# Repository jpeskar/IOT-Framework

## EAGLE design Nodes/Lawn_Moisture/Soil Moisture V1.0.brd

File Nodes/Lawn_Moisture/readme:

Lawn Moisture Sensor

Consists of a Vegetronix VH400 and two (2) Dallas DS18S20 one wire thermometers. The internal thermometer is used for tuning the radio and the external is for maping ground 
temperature.

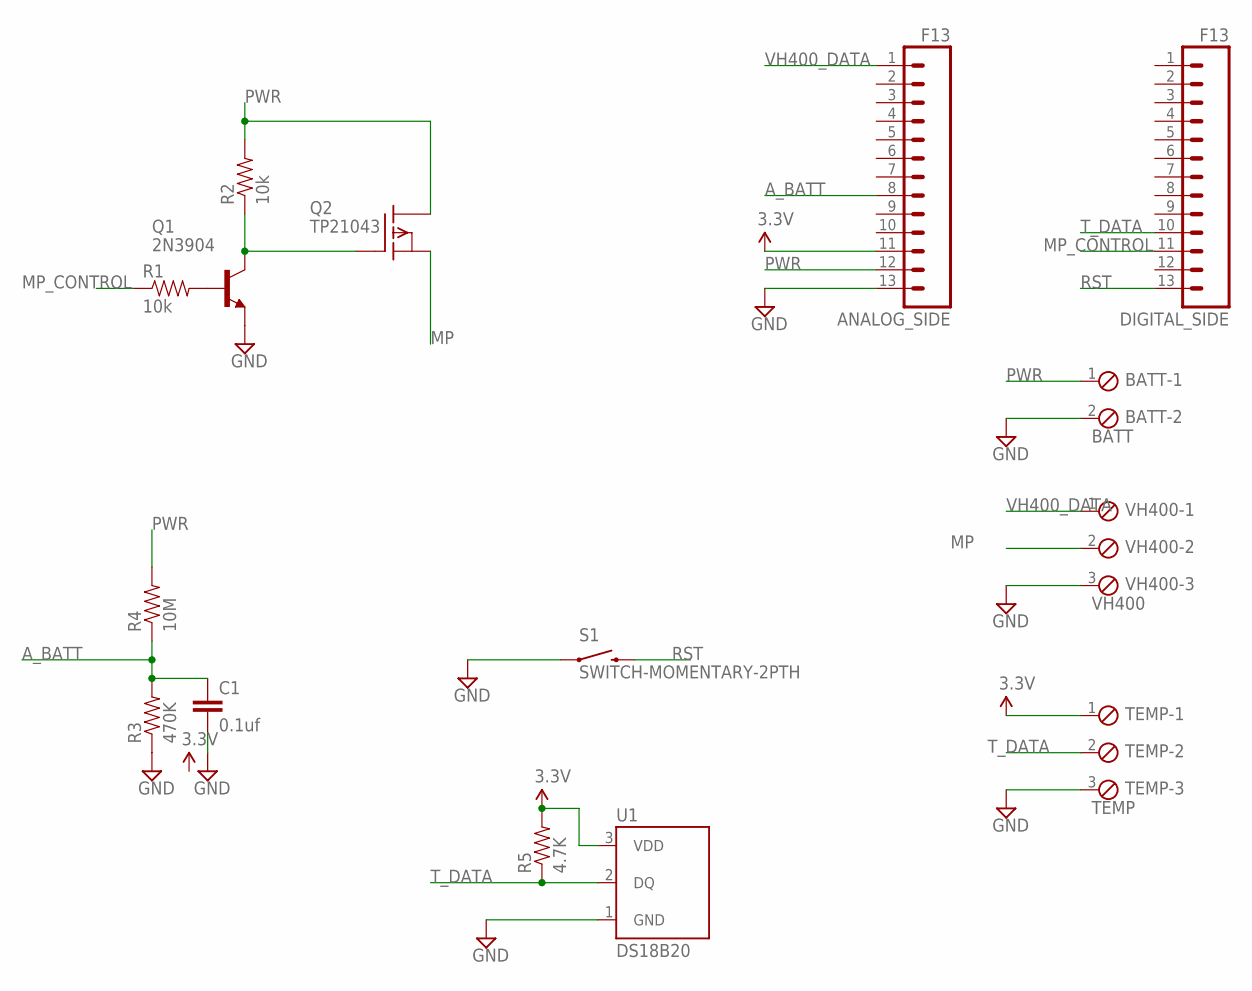
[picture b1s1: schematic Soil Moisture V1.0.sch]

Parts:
ANALOG_SIDE: F13; 1X13
BATT: BATT; 2POL254
C1: 0.1uf; CAP-PTH-SMALL-KIT
DIGITAL_SIDE: F13; 1X13
Q1: 2N3904; TO92
Q2: TP21043; TO92
R1, R2: 10k; AXIAL-0.3EZ
R3: 470K; AXIAL-0.3
R4: 10M; AXIAL-0.3
R5: 4.7K; AXIAL-0.3
S1: SWITCH-MOMENTARY-2PTH; TACTILE-PTH
TEMP: TEMP; 3POL254
U1: DS18B20; TO-92-AMMO
VH400: VH400; 3POL254

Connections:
3.3V: ANALOG_SIDE.11, R5.P$2 (2), TEMP.1, U1.3 (VDD)
A_BATT: ANALOG_SIDE.8, C1.1, R3.P$2 (2), R4.P$1 (1)
GND: ANALOG_SIDE.13, BATT.2, C1.2, Q1.3 (E), R3.P$1 (1), S1.1, TEMP.3, U1.1 (GND), VH400.3
MP: Q2.1 (S), VH400.2
MP_CONTROL: DIGITAL_SIDE.11, R1.P$1 (1)
unnamed: Q1.2 (B), R1.P$2 (2)
unnamed: Q1.1 (C), Q2.2 (G), R2.P$1 (1)
PWR: ANALOG_SIDE.12, BATT.1, Q2.3 (D), R2.P$2 (2), R4.P$2 (2)
RST: DIGITAL_SIDE.13, S1.3 (2)
T_DATA: DIGITAL_SIDE.10, R5.P$1 (1), TEMP.2, U1.2 (DQ)
VH400_DATA: ANALOG_SIDE.1, VH400.1

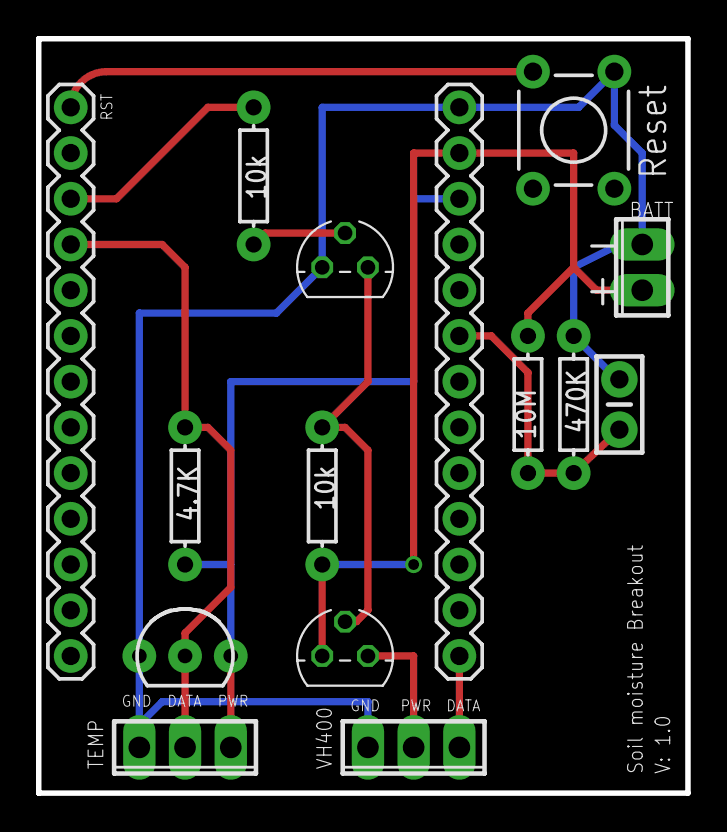
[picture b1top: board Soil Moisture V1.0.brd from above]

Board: 2 copper layers, 36.1 x 41.9 mm, 15 parts (0 on the bottom side), 11 nets.

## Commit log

2015-12-27 Create Lawn_Moisture
2015-12-27 Create Node_Libraries
2015-12-27 first commit of lawn moisture node
2015-12-27 code re-factoring
2015-12-28 re-factor new node functions
    Re-factored the capture of a new nodes identity to include a catch of
    not capturing a return message.
2016-01-02 update readme
    update Lawn Moisture Readme
2016-01-03 move radio.sleep
    move radio.sleep in the main program to a more sensible location
2016-01-03 add lib and re-factor lawn moisture
    add lib for battery management and a library for compiling messages.
2016-01-05 latest updates
2016-01-23 New Includes
    New or updated includes.
2016-01-23 Added Lawn Moisture Hardware
    V: 1.O hardware added
2016-01-23 Update to Gateway Code
2016-02-19 Add structures instead of char string
2016-04-25 added lawn moisture struct
2016-04-29 Program flow charts added
2016-04-29 Added files via upload
2016-05-05 big refactor
2017-05-07 server connector file
2017-05-07 not needed

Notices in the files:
parts and their libraries:
SparkFun-Connectors: Licensing: Creative Commons ShareAlike 4.0 International - https://creativecommons.org/licenses/by-sa/4.0
